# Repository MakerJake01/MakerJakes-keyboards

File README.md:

# MakerJake's-keyboards
## Index and Info about my keyboards. 
Stil a WIP some links might not work.
| key |   |
| ----------- | ---------- |
| :white_check_mark: | done |
| :construction: | under construction |
| ❌ | little to no info |

For the most up to date information join my discord server.
<br>  

## [BabyvBle](https://github.com/MakerJake01/MakerJakes-keyboards/tree/main/BabyvBle)

The BabyvBle is a [Nice!Nano](https://nicekeyboards.com/nice-nano/) based choc v1 keyboard with an layout modified from the BabyV by [Eye Oh Designs](https://www.instagram.com/eyeohdesigns/?hl=en) and an optional oled. 

Complete? :white_check_mark: 

## [J46K](https://github.com/MakerJake01/J46K)

The J46K is a 4x12 choc ortho keyboard that uses a PM and has an oled. 

Complete? :white_check_mark:

## [J46Kcol](https://github.com/MakerJake01/MakerJakes-keyboards/tree/main/J46kcol)

The J46Kcol is a hotswap PM based split unibody cherry spaced choc columnar stagger tray mount keyboard with perkey rgb backlighting.

Complete? :white_check_mark:

## [J46KcolMx](https://github.com/MakerJake01/MakerJakes-keyboards/tree/main/J46KcolMx)

The J46KcolMx is a hotswap PM based split unibody Mx columnar stagger bottom mount with and oled keyboard.

## [J46KcolS](https://github.com/MakerJake01/MakerJakes-keyboards/tree/main/J46KcolS)

The J46KcolS is a hotswap [Nice!Nano](https://nicekeyboards.com/nice-nano/) based split cherry spaced choc columnar stagger keyboard with encoders.

Complete? :construction:

## [J46Kbm](https://github.com/MakerJake01/MakerJakes-keyboards/tree/main/J46Kbm)

The J46Kbm is a hotswap bottom mount ortho keyboard. 

Complete? :construction:

## [Trailmax](https://github.com/MakerJake01/MakerJakes-keyboards/tree/main/Trailmax)

The trailmax is a totally original choc ortho split keyboard. 

Complete? :construction:

## [Tesseract](https://github.com/MakerJake01/MakerJakes-keyboards/tree/main/Tesseract)

The tesseract is a atmega328p based mx hotswap ortho keyboard. 

Complete? :construction:

## [J46Kr](https://github.com/MakerJake01/MakerJakes-keyboards/tree/main/J46Kr)

The J46Kr is a promicro based split keyboard hotswap keyboard with back lighting and an OLED.  

Complete? :construction:

## [J46Kvan](https://github.com/MakerJake01/MakerJakes-keyboards/tree/main/J46Kvan)

The J46Kvan is a minivan sized atmega328p based mx hotswap ortho keyboard. 

Complete? :construction:

## [J46Kx](https://github.com/MakerJake01/MakerJakes-keyboards/tree/main/J46Kx)

The J46Kx is a bluetooth 12u ortho reversible Seeeduino Xiao based keyboard.

Complete? :white_check_mark:

## [J42K & J42Ki](https://github.com/MakerJake01/MakerJakes-keyboards/tree/main/J42K)

The J42K is a PM based tray mount 12u HHKB ortho hotswap keyboard. The J42Ki is uses an integrated controller.

Complete? :construction:

## [J42Kbm](https://github.com/MakerJake01/MakerJakes-keyboards/tree/main/J42Kbm)

The J42K is a bottom mount 12u HHKB ortho hotswap keyboard.

Complete? :construction:

## [J47K](https://github.com/MakerJake01/MakerJakes-keyboards/tree/main/J47K)

The J47K is a hotswap gasket mount ortho keyboard with dedicated arrows and an oled.

Complete? :construction:

## [Modular USB Hub](https://github.com/MakerJake01/MakerJakes-keyboards/tree/main/Mdhcudbcusbhb)

This is a modular USB hub system built around the Mdhcudbcusbhb with peripheral boards made to be compatible with the UDB JST cable.

Complete? :construction:

## [J0k](https://github.com/MakerJake01/MakerJakes-keyboards/tree/main/J0K)

The J0K is a EC12 compatible knob with an M2 set screw.

Complete? :white_check_mark:

## [J73K](https://github.com/MakerJake01/J73K_keyboard)

The J73K is a 15x5 ortholinear mainly tht keyboard with an atmega32a and USB C.  

# Naming scheme 
The way I name my keyboards is quite repetitive, for many it can be a point of confusion. 
 
<br>Most of my keyboards follow this naming convention because I can't think of new names so I use this.
## Breaking down the name 
The name has one main part, the starting bit. They all have a J##K, the number is the number of keys in the build. This helps me differentiate boards with different layouts. 
## The Suffix
As many might have noticed there are many boards with the same layout. The suffix allows me to add a bit of info to the name and keep the projects apart. There is no real rule for what the suffix has to be. The *Mx* in *J46KcolMx* tells me that this board uses Mx switches. Others can now guess the name of the board just by looking at it. 
<br> 
<br>  albeit with varying success.

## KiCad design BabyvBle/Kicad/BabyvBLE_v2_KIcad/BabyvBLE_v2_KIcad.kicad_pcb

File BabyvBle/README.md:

# BabyvBle
### [Back to main list of boards](https://github.com/MakerJake01/MakerJakes-keyboards) 

## The BabyvBle is a Nice!Nano based choc v1 keyboard with an layout modified from the BabyV by [Eye Oh Designs](https://www.instagram.com/eyeohdesigns/?hl=en)

The keyboard has a spacing of 19.05x19.05. The layout is the same as the full size Babyv but there are two extra keys next to the thumb cluster. Both sides have the choice between 1x2u and 2x1u bottom rows. There is also the option of a front or back JST. The backplate is reversible.

## PCB

Provided in this repo are both gerber files for manufacturing and there are KiCad files for your own modifications. 

## Firmware

The firmware used for this is [ZMK](https://github.com/MakerJake01/zmk/tree/main/app/boards/shields/babyvble) but it can work with QMK. The current firmware files are not up to date with ZMK however it is functional.

## Changes in V2.1
- Slightly recessed power switch to stop them from breaking when not in use 
- Added + and - labels to the JST footprint 
- Added labels to the I2C header

# Parts
| Part        | Number      | Note |
| :---        |    :----:   |          ---: |
| Nice!Nano   | 1           | could be replaced with PM if you dont want bluetooth |
| Hotswap Sockets | 46-48  | |
| Choc Switches |46-48 |Choc v1 |
| 1N4148   | 46-48        | DO-35      |
| Headers  | 24 | For PM |
| Stand Offs | 8-10 | M2 |
| Screws | 16-20 | M2 at least 3mm | 
| JST | 1 | JST PH SMD not needed but recommended |
| Reset Button | 1 | 6x6 SMD | 
| Power Switch | 1 | PCM12 | 
| Screw In Feet | 2 | They are nice for typing but not needed | 

# Where to Buy 
I am working on a group buy but in lieu of any plans my discord will be the best place to get up to date info. 

Go to the `#choose-roles` channel and type 
~~~
!join BabyvBle
~~~

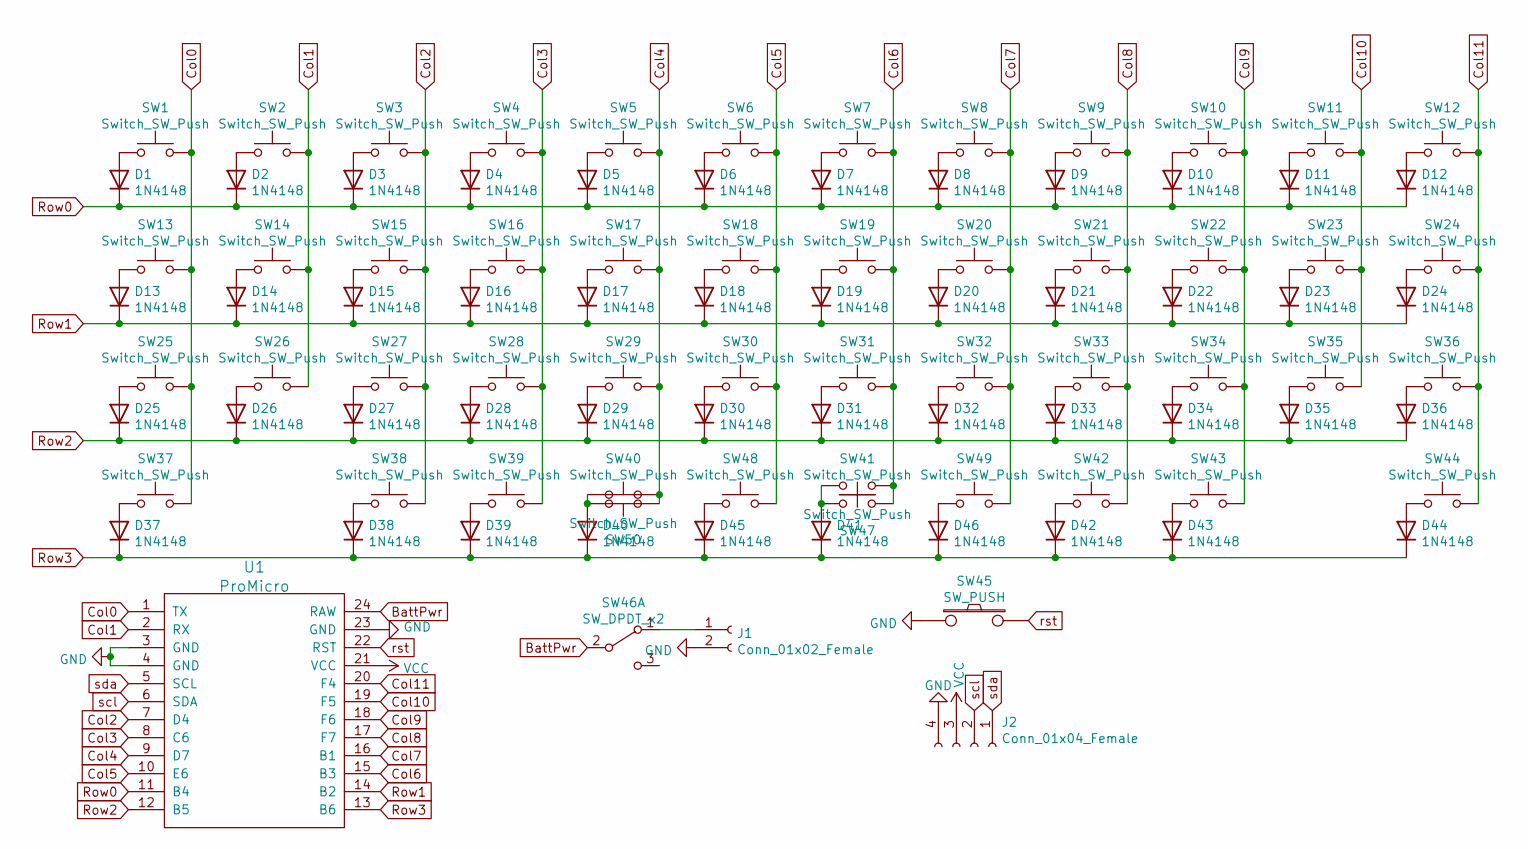
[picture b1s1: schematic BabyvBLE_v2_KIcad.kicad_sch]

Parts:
D1, D2, D3, D4, D5, D6, D7, D8, D9, D10, D11, D12, D13, D14, D15, D16, D17, D18, D19, D20, D21, D22, D23, D24, D25, D26, D27, D28, D29, D30, D31, D32, D33, D34, D35, D36, D37, D38, D39, D40, D41, D42, D43, D44, D45, D46: 1N4148; D_DO-35_SOD27 with out the damn K or maybe the number thing
J1: Conn_01x02_Female; JST_PH_S2B-PH-SM4-TB_1x02-1MP_P2.00mm_Horizontal_BothSides
J2: Conn_01x04_Female; PinHeader_1x04_P2.54mm_Vertical
SW1, SW2, SW3, SW4, SW5, SW6, SW7, SW8, SW9, SW10, SW11, SW12, SW13, SW14, SW15, SW16, SW17, SW18, SW19, SW20, SW21, SW22, SW23, SW24, SW25, SW26, SW27, SW28, SW29, SW30, SW31, SW32, SW33, SW34, SW35, SW36, SW37, SW38, SW39, SW40, SW41, SW42, SW43, SW44, SW47, SW48, SW49, SW50: Switch_SW_Push; Kailh_socket_PG1350_no_corner_box_user drawing
SW45: SW_PUSH; SW_Push_1P1T_NO_6x6mm_H9.5mm
SW46: SW_DPDT_x2; SW_SPDT_PCM12
U1: ProMicro; ArduinoProMicro

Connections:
BattPwr: SW46.2 (B), U1.24 (RAW)
Col0: SW1.2, SW13.2, SW25.2, SW37.2, U1.1 (TX)
Col1: SW2.2, SW14.2, SW26.2, U1.2 (RX)
Col2: SW3.2, SW15.2, SW27.2, SW38.2, U1.7 (D4)
Col3: SW4.2, SW16.2, SW28.2, SW39.2, U1.8 (C6)
Col4: SW5.2, SW17.2, SW29.2, SW40.2, SW50.1, U1.9 (D7)
Col5: SW6.2, SW18.2, SW30.2, SW48.2, U1.10 (E6)
Col6: SW7.2, SW19.2, SW31.2, SW41.2, SW47.1, U1.15 (B3)
Col7: SW8.2, SW20.2, SW32.2, SW49.2, U1.16 (B1)
Col8: SW9.2, SW21.2, SW33.2, SW42.2, U1.17 (F7)
Col9: SW10.2, SW22.2, SW34.2, SW43.2, U1.18 (F6)
Col10: SW11.2, SW23.2, SW35.2, U1.19 (F5)
Col11: SW12.2, SW24.2, SW36.2, SW44.2, U1.20 (F4)
GND: J1.2, J2.4, SW45.1, U1.3 (GND), U1.4 (GND), U1.23 (GND)
unnamed: D1.2 (A), SW1.1
unnamed: D2.2 (A), SW2.1
unnamed: D3.2 (A), SW3.1
unnamed: D4.2 (A), SW4.1
unnamed: D5.2 (A), SW5.1
unnamed: D6.2 (A), SW6.1
unnamed: D7.2 (A), SW7.1
unnamed: D8.2 (A), SW8.1
unnamed: D9.2 (A), SW9.1
unnamed: D10.2 (A), SW10.1
unnamed: D11.2 (A), SW11.1
unnamed: D12.2 (A), SW12.1
unnamed: D13.2 (A), SW13.1
unnamed: D14.2 (A), SW14.1
unnamed: D15.2 (A), SW15.1
unnamed: D16.2 (A), SW16.1
unnamed: D17.2 (A), SW17.1
unnamed: D18.2 (A), SW18.1
unnamed: D19.2 (A), SW19.1
unnamed: D20.2 (A), SW20.1
unnamed: D21.2 (A), SW21.1
unnamed: D22.2 (A), SW22.1
unnamed: D23.2 (A), SW23.1
unnamed: D24.2 (A), SW24.1
unnamed: D25.2 (A), SW25.1
unnamed: D26.2 (A), SW26.1
unnamed: D27.2 (A), SW27.1
unnamed: D28.2 (A), SW28.1
unnamed: D29.2 (A), SW29.1
unnamed: D30.2 (A), SW30.1
unnamed: D31.2 (A), SW31.1
unnamed: D32.2 (A), SW32.1
unnamed: D33.2 (A), SW33.1
unnamed: D34.2 (A), SW34.1
unnamed: D35.2 (A), SW35.1
unnamed: D36.2 (A), SW36.1
unnamed: D37.2 (A), SW37.1
unnamed: D38.2 (A), SW38.1
unnamed: D39.2 (A), SW39.1
unnamed: D40.2 (A), SW40.1, SW50.2
unnamed: D41.2 (A), SW41.1, SW47.2
unnamed: D42.2 (A), SW42.1
unnamed: D43.2 (A), SW43.1
unnamed: D44.2 (A), SW44.1
unnamed: D45.2 (A), SW48.1
unnamed: D46.2 (A), SW49.1
unnamed: J1.1, SW46.1 (A)
Row0: D1.1 (K), D2.1 (K), D3.1 (K), D4.1 (K), D5.1 (K), D6.1 (K), D7.1 (K), D8.1 (K), D9.1 (K), D10.1 (K), D11.1 (K), D12.1 (K), U1.11 (B4)
Row1: D13.1 (K), D14.1 (K), D15.1 (K), D16.1 (K), D17.1 (K), D18.1 (K), D19.1 (K), D20.1 (K), D21.1 (K), D22.1 (K), D23.1 (K), D24.1 (K), U1.14 (B2)
Row2: D25.1 (K), D26.1 (K), D27.1 (K), D28.1 (K), D29.1 (K), D30.1 (K), D31.1 (K), D32.1 (K), D33.1 (K), D34.1 (K), D35.1 (K), D36.1 (K), U1.12 (B5)
Row3: D37.1 (K), D38.1 (K), D39.1 (K), D40.1 (K), D41.1 (K), D42.1 (K), D43.1 (K), D44.1 (K), D45.1 (K), D46.1 (K), U1.13 (B6)
VCC: J2.3, U1.21 (VCC)
rst: SW45.2, U1.22 (RST)
scl: J2.2, U1.6 (SDA)
sda: J2.1, U1.5 (SCL)

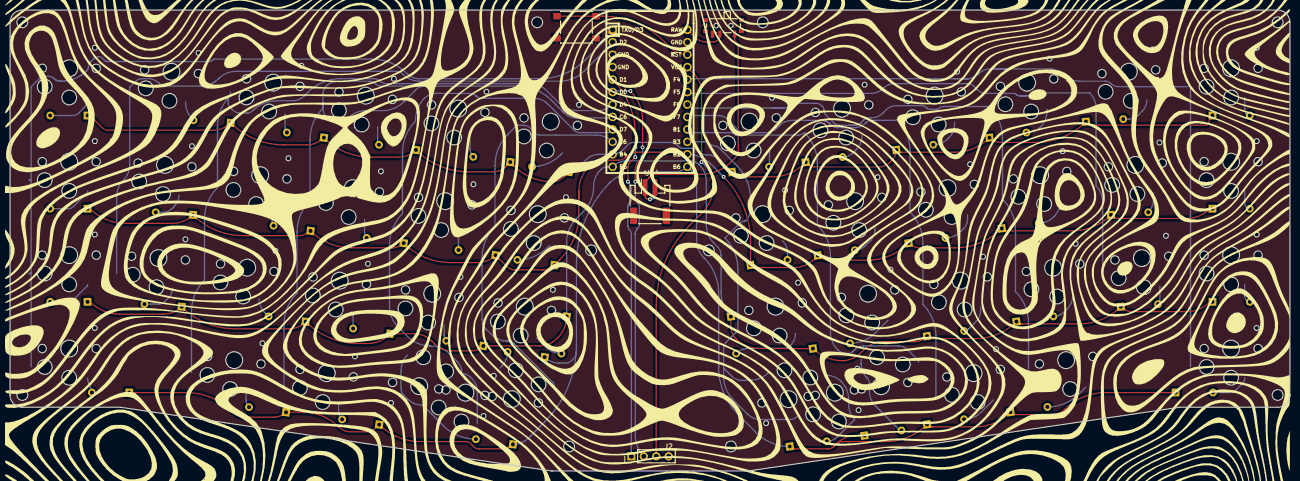
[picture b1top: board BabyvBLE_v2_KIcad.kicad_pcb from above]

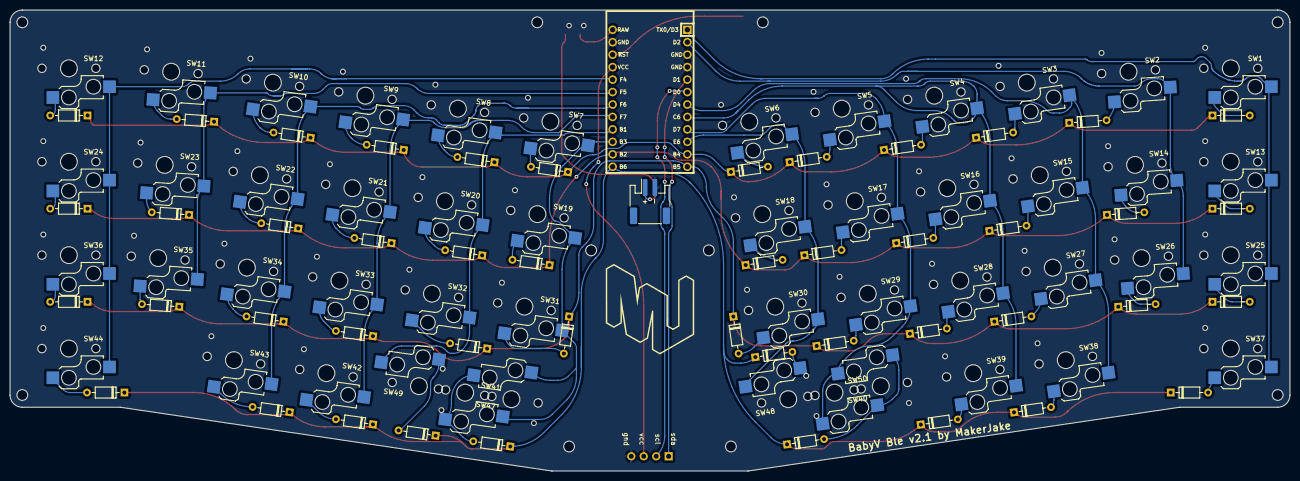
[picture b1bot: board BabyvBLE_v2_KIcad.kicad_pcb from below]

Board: 2 copper layers, 261.0 x 94.0 mm, 99 parts (46 on the bottom side), 69 nets.

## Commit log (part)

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2022-03-17 added babyvble to main readme
2022-03-17 added more info
2022-03-17 added hyperlink
2022-03-17 changed switch info
2022-03-18 fixed link and added J46K
2022-03-18 added but no links
2022-03-18 adding hyperlinks
2022-03-18 added the images maybr
2022-03-18 added stuffs
2022-03-18 fixing things and adding info for the J46Kcol
2022-03-18 even more info and stuffs
2022-03-18 fixed some links and added col mx info and files
2022-03-21 fixing links
2022-03-21 fixed grammar and added J46KcolS info
2022-04-08 doing what I can on my chrome book.
2022-04-08 staching these changes casue I dont want to lose them.
2022-05-02 adding images
2022-05-03 adding in readme templates to the folders
2022-05-10 small changes
2022-08-29 added the image
2022-08-29 added image and basic description
    I don't like homeroom
2022-08-31 more info about the tesseract
2022-10-14 added more info and expanded trailmax
2022-10-14 added j42ki and more info
2022-11-21 adding in how complete each page is
2022-11-21 added a key
2023-03-18 added parts list
2024-06-30 Added footprint library and reference where they were acquired from.
2024-06-30 Added babyvble kicad and gerber files.
    Added more footprints and where they cam from.
2024-06-30 Improved J42Ki information and moved it to be under J42K
2024-07-22 Added extended key compat info
    I had a revelation
2024-07-23 added J46Kvan
2024-07-23 added tesseract back
2024-07-23 fixed link
2024-07-23 changed pic and fixed spelling
2024-07-27 changed possible layouts
2024-08-02 Added to J46Kvan. Created J46Kx and J46Kr info.
2024-12-23 added J0k
2024-12-23 Added J46Kx v1 pcb and case files
2024-12-23 Added gerber files for J46Kcols and expanded info for J46Kx
2024-12-23 Fixed name of READMEs
2024-12-23 Added KiCad files for J46Kx and associated footprints
2024-12-23 Added more footprints to lib
2024-12-23 Added J42Kbm info
2025-09-06 Added more info for J42Kbm
    Will add kicad files in the near future
